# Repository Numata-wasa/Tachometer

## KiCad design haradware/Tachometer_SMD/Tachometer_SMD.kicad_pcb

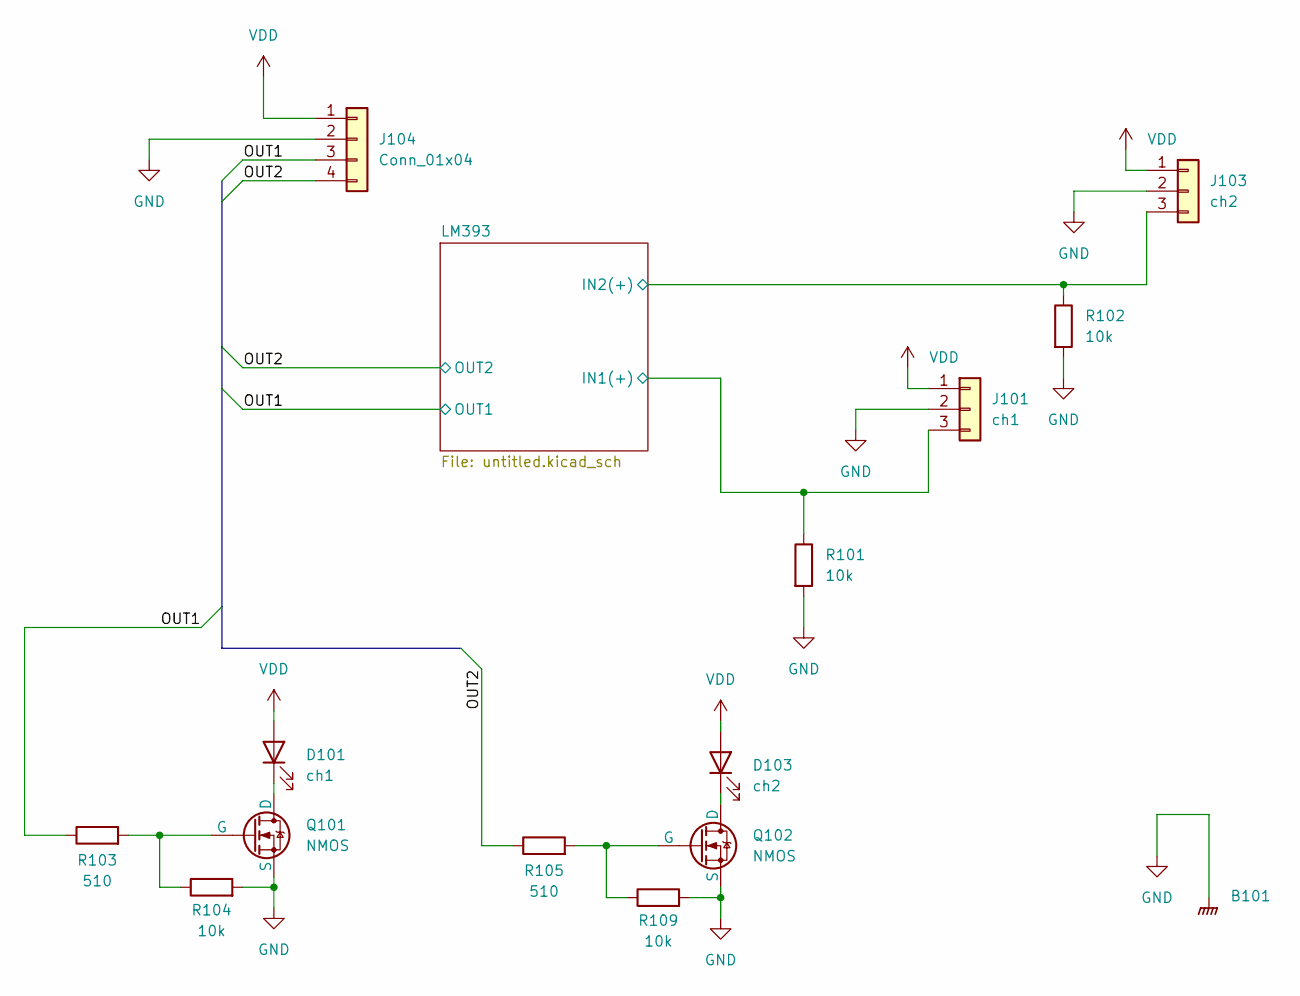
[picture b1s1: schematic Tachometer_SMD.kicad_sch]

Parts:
B101: Board_1U_60x60
D101: ch1; LED_0805_2012Metric
D103: ch2; LED_0805_2012Metric
J101: ch1; JST_PH_B3B-PH-K_1x03_P2.00mm_Vertical
J103: ch2; JST_PH_B3B-PH-K_1x03_P2.00mm_Vertical
J104: Conn_01x04; JST_XH_S4B-XH-A_1x04_P2.50mm_Horizontal
Q101, Q102: NMOS; TSOT-23
R101, R102, R104, R109: 10k; R_0402_1005Metric
R103, R105: 510; R_0402_1005Metric

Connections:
/LM393/IN1(+): J101.3, R101.1; also elsewhere on the board
/LM393/IN2(+): J103.3, R102.1; also elsewhere on the board
/OUT1: J104.3, R103.1; also elsewhere on the board
/OUT2: J104.4, R105.1; also elsewhere on the board
GND: B101.GND, J101.2, J103.2, J104.2, Q101.3 (S), Q102.3 (S), R101.2, R102.2, R104.2, R109.2; also elsewhere on the board
unnamed: D101.1 (K), Q101.1 (D)
unnamed: D103.1 (K), Q102.1 (D)
unnamed: Q101.2 (G), R103.2, R104.1
unnamed: Q102.2 (G), R105.2, R109.1
VDD: D101.2 (A), D103.2 (A), J101.1, J103.1, J104.1; also elsewhere on the board

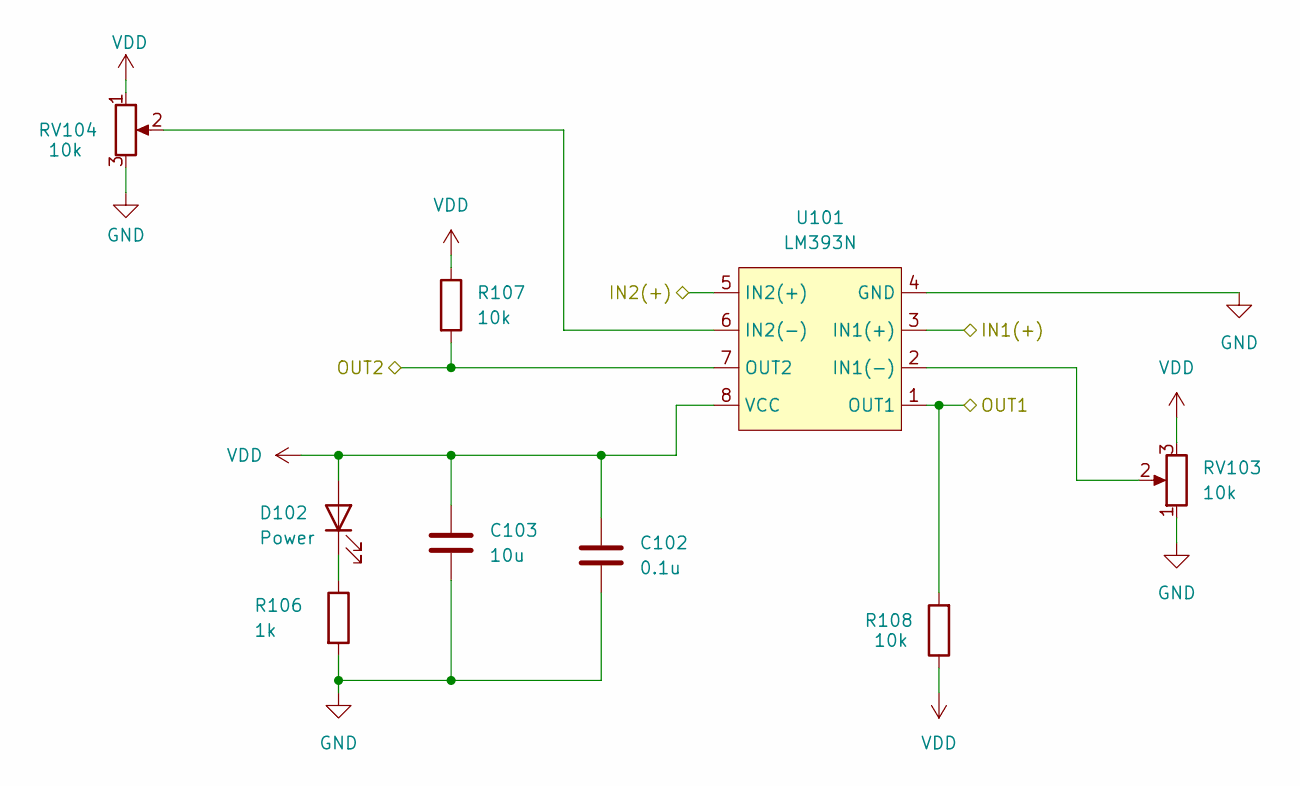
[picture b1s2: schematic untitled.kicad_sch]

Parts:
C102: 0.1u; C_0402_1005Metric
C103: 10u; C_0201_0603Metric
D102: Power; LED_0805_2012Metric
R106: 1k; R_0402_1005Metric
R107, R108: 10k; R_0402_1005Metric
RV103, RV104: 10k; Potentiometer_Bourns_3296P_Horizontal
U101: LM393N; JEITA_SOIC-8_3.9x4.9mm_P1.27mm

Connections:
/LM393/IN1(+): U101.3 (IN1(+)); also elsewhere on the board
/LM393/IN2(+): U101.5 (IN2(+)); also elsewhere on the board
/OUT1: R108.2, U101.1 (OUT1); also elsewhere on the board
/OUT2: R107.2, U101.7 (OUT2); also elsewhere on the board
GND: C102.2, C103.2, R106.2, RV103.1, RV104.3, U101.4 (GND); also elsewhere on the board
unnamed: D102.1 (K), R106.1
unnamed: RV103.2, U101.2 (IN1(-))
unnamed: RV104.2, U101.6 (IN2(-))
VDD: C102.1, C103.1, D102.2 (A), R107.1, R108.1, RV103.3, RV104.1, U101.8 (VCC); also elsewhere on the board

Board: 2 copper layers, 23 parts (0 on the bottom side), 13 nets, no tracks yet.

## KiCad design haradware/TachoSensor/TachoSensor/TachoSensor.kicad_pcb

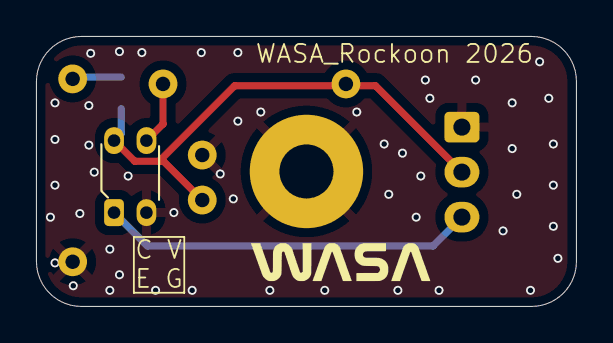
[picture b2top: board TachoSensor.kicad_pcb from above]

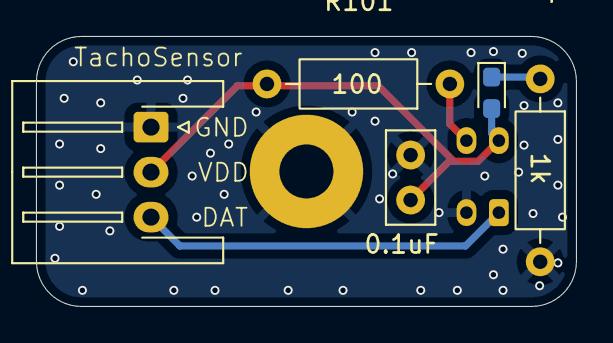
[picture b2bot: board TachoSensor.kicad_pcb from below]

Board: 2 copper layers, 30.0 x 15.0 mm, 6 parts (5 on the bottom side), 5 nets.

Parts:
0.1uF: 0.1uF; C_Disc_D5.0mm_W2.5mm_P2.50mm
D101: PWR; LED_0603_1608Metric_Pad1.05x0.95mm_HandSolder
J101: OUT; JST_XH_S3B-XH-A-1_1x03_P2.50mm_Horizontal
R101: 100; R_Axial_DIN0207_L6.3mm_D2.5mm_P10.16mm_Horizontal
R102: 1k; R_Axial_DIN0207_L6.3mm_D2.5mm_P10.16mm_Horizontal
U101: RPR-220; Everlight_ITR8307F43

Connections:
GND: 0.1uF.2, J101.1 (Pin_3), R102.2, U101.2 (K)
unnamed: 0.1uF.1, D101.2 (A), J101.2, R101.2, U101.4 (4C)
unnamed: D101.1 (K), R102.1
unnamed: J101.3 (Pin_1), U101.3 (E)
unnamed: R101.1, U101.1 (A)

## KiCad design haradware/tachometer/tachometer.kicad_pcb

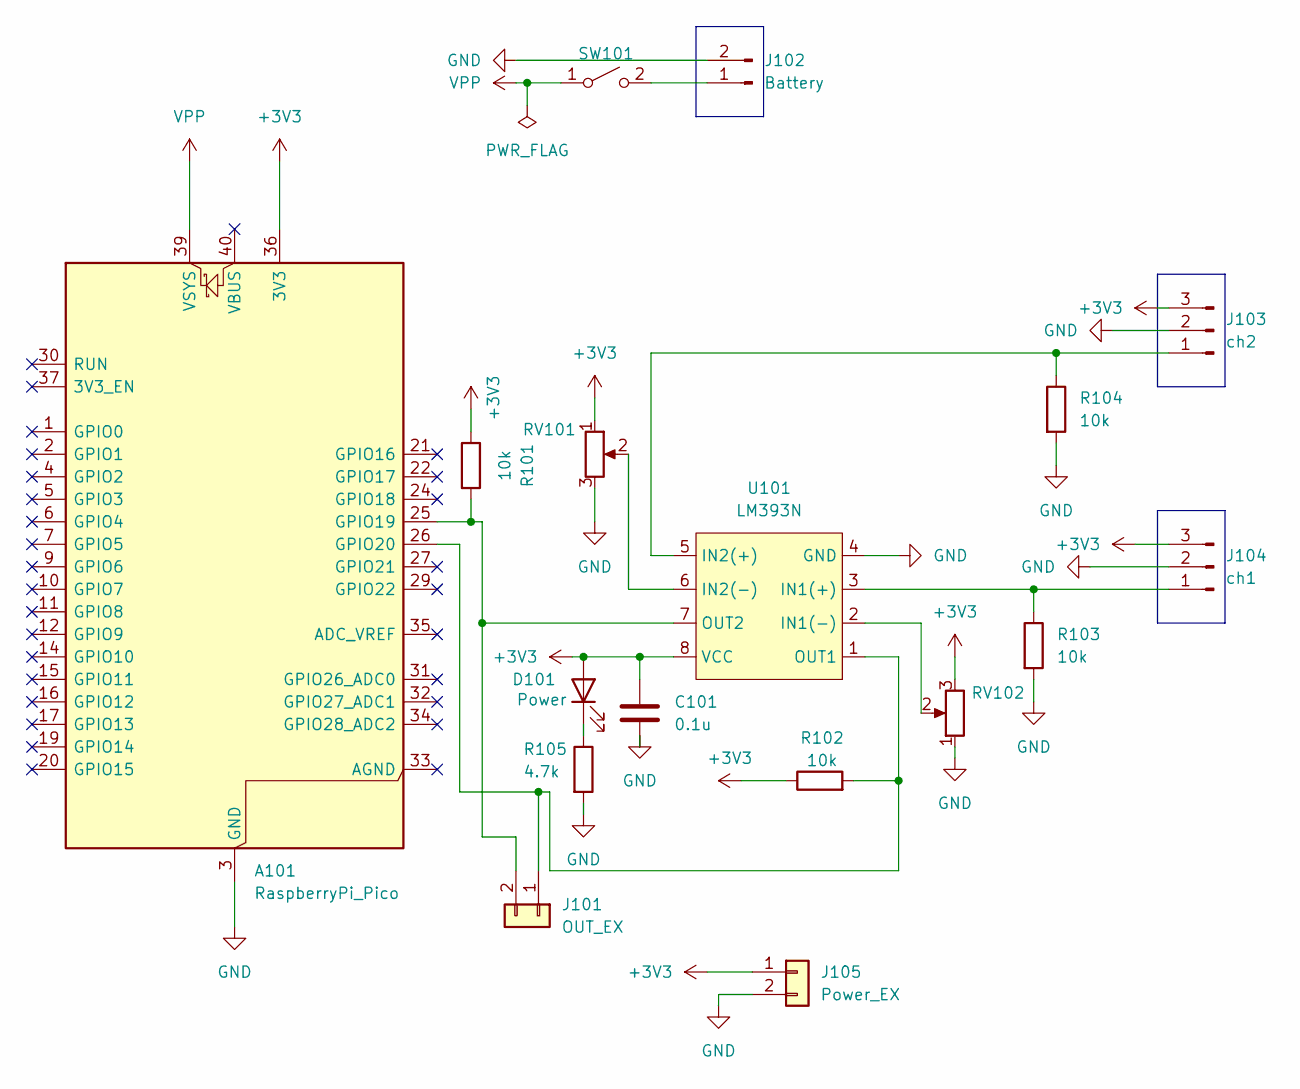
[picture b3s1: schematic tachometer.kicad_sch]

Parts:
A101: RaspberryPi_Pico; RaspberryPi_Pico_Common_Unspecified
C101: 0.1u; C_Axial_L5.1mm_D3.1mm_P10.00mm_Horizontal
D101: Power; LED_D5.0mm
J101: OUT_EX; PinHeader_1x02_P2.54mm_Vertical
J102: Battery; JST_PH_B2B-PH-K_1x02_P2.00mm_Vertical
J103: ch2; JST_PH_B3B-PH-K_1x03_P2.00mm_Vertical
J104: ch1; JST_PH_B3B-PH-K_1x03_P2.00mm_Vertical
J105: Power_EX; PinHeader_1x02_P2.54mm_Vertical
R101, R102, R103, R104: 10k; R_Axial_DIN0207_L6.3mm_D2.5mm_P7.62mm_Horizontal
R105: 4.7k; R_Axial_DIN0207_L6.3mm_D2.5mm_P7.62mm_Horizontal
RV101, RV102: R_Potentiometer; Potentiometer_Bourns_3296P_Horizontal
SW101: SW_SPST; SW_Slide-03_Wuerth-WS-SLTV_10x2.5x6.4_P2.54mm
U101: LM393N; CERDIP-8_W7.62mm_SideBrazed

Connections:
+3V3: A101.36 (3V3), C101.1, D101.2 (A), J103.3, J104.3, J105.1, R101.1, R102.1, RV101.1, RV102.3, U101.8 (VCC)
GND: A101.3 (GND), A101.8 (GND), A101.13 (GND), A101.18 (GND), A101.23 (GND), A101.28 (GND), A101.38 (GND), C101.2, J102.2, J103.2, J104.2, J105.2, R103.2, R104.2, R105.2, RV101.3, RV102.1, U101.4 (GND)
unnamed: A101.25 (GPIO19), J101.2, R101.2, U101.7 (OUT2)
unnamed: A101.26 (GPIO20), J101.1, R102.2, U101.1 (OUT1)
unnamed: D101.1 (K), R105.1
unnamed: J102.1, SW101.2 (B)
unnamed: J103.1, R104.1, U101.5 (IN2(+))
unnamed: J104.1, R103.1, U101.3 (IN1(+))
unnamed: RV102.2, U101.2 (IN1(-))
unnamed: RV101.2, U101.6 (IN2(-))
VPP: A101.39 (VSYS), SW101.1 (A)

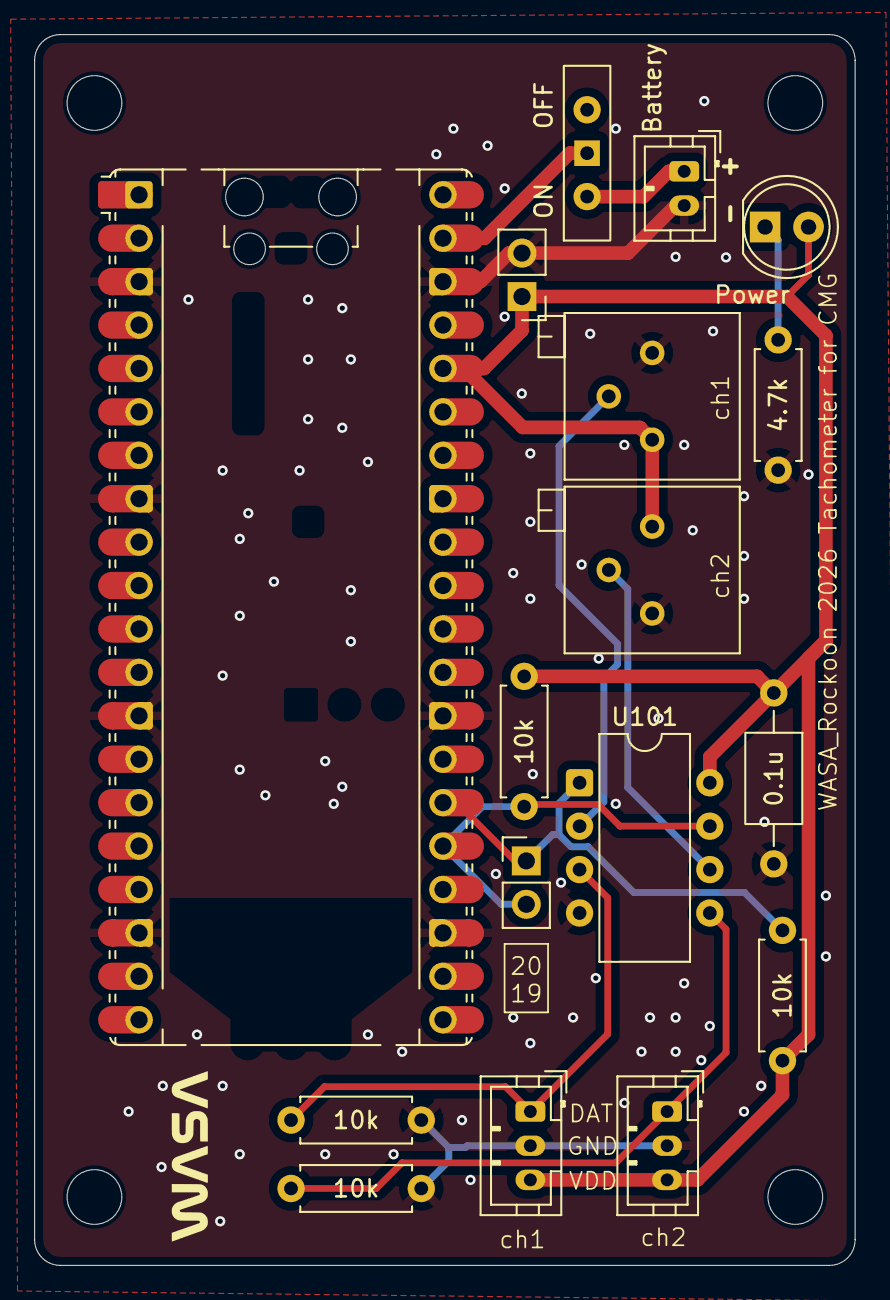
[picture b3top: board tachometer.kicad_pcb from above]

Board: 2 copper layers, 48.0 x 72.0 mm, 17 parts (0 on the bottom side), 11 nets.

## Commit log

2025-12-11 Rename project from 'rockoon_personal' to 'tachometer'
2025-12-12 平均をとて表示する用に変更
2025-12-12 Revert "平均をとて表示する用に変更"
    This reverts commit 1b32300a3aa4ac1fc7abaa99a969809da4aa486a.
2025-12-12 Reapply "平均をとて表示する用に変更"
    This reverts commit afaf4f43e88ea4427e46e7c872ad655bb13d77ee.
2026-01-03 KiCAD途中
2026-01-13 KiCad編集
2026-02-07 修正して再発注
2026-02-09 センサーの基板作成 確認後発注可能
2026-02-12 白黒判定のコードを追加
2026-02-14 シルク追加してガーバー出力
2026-02-15 SMDタイプの設計．PWRLEDを追加
2026-02-17 なんだかわからない更新
2026-02-20 SMD用のフォルダを作成
2026-02-20 つくった
2026-02-20 ちょっときれいに
2026-02-20 フットプリント割り当て
2026-02-20 WOBCライブラリをピン留め
2026-02-20 ちょっと整理
